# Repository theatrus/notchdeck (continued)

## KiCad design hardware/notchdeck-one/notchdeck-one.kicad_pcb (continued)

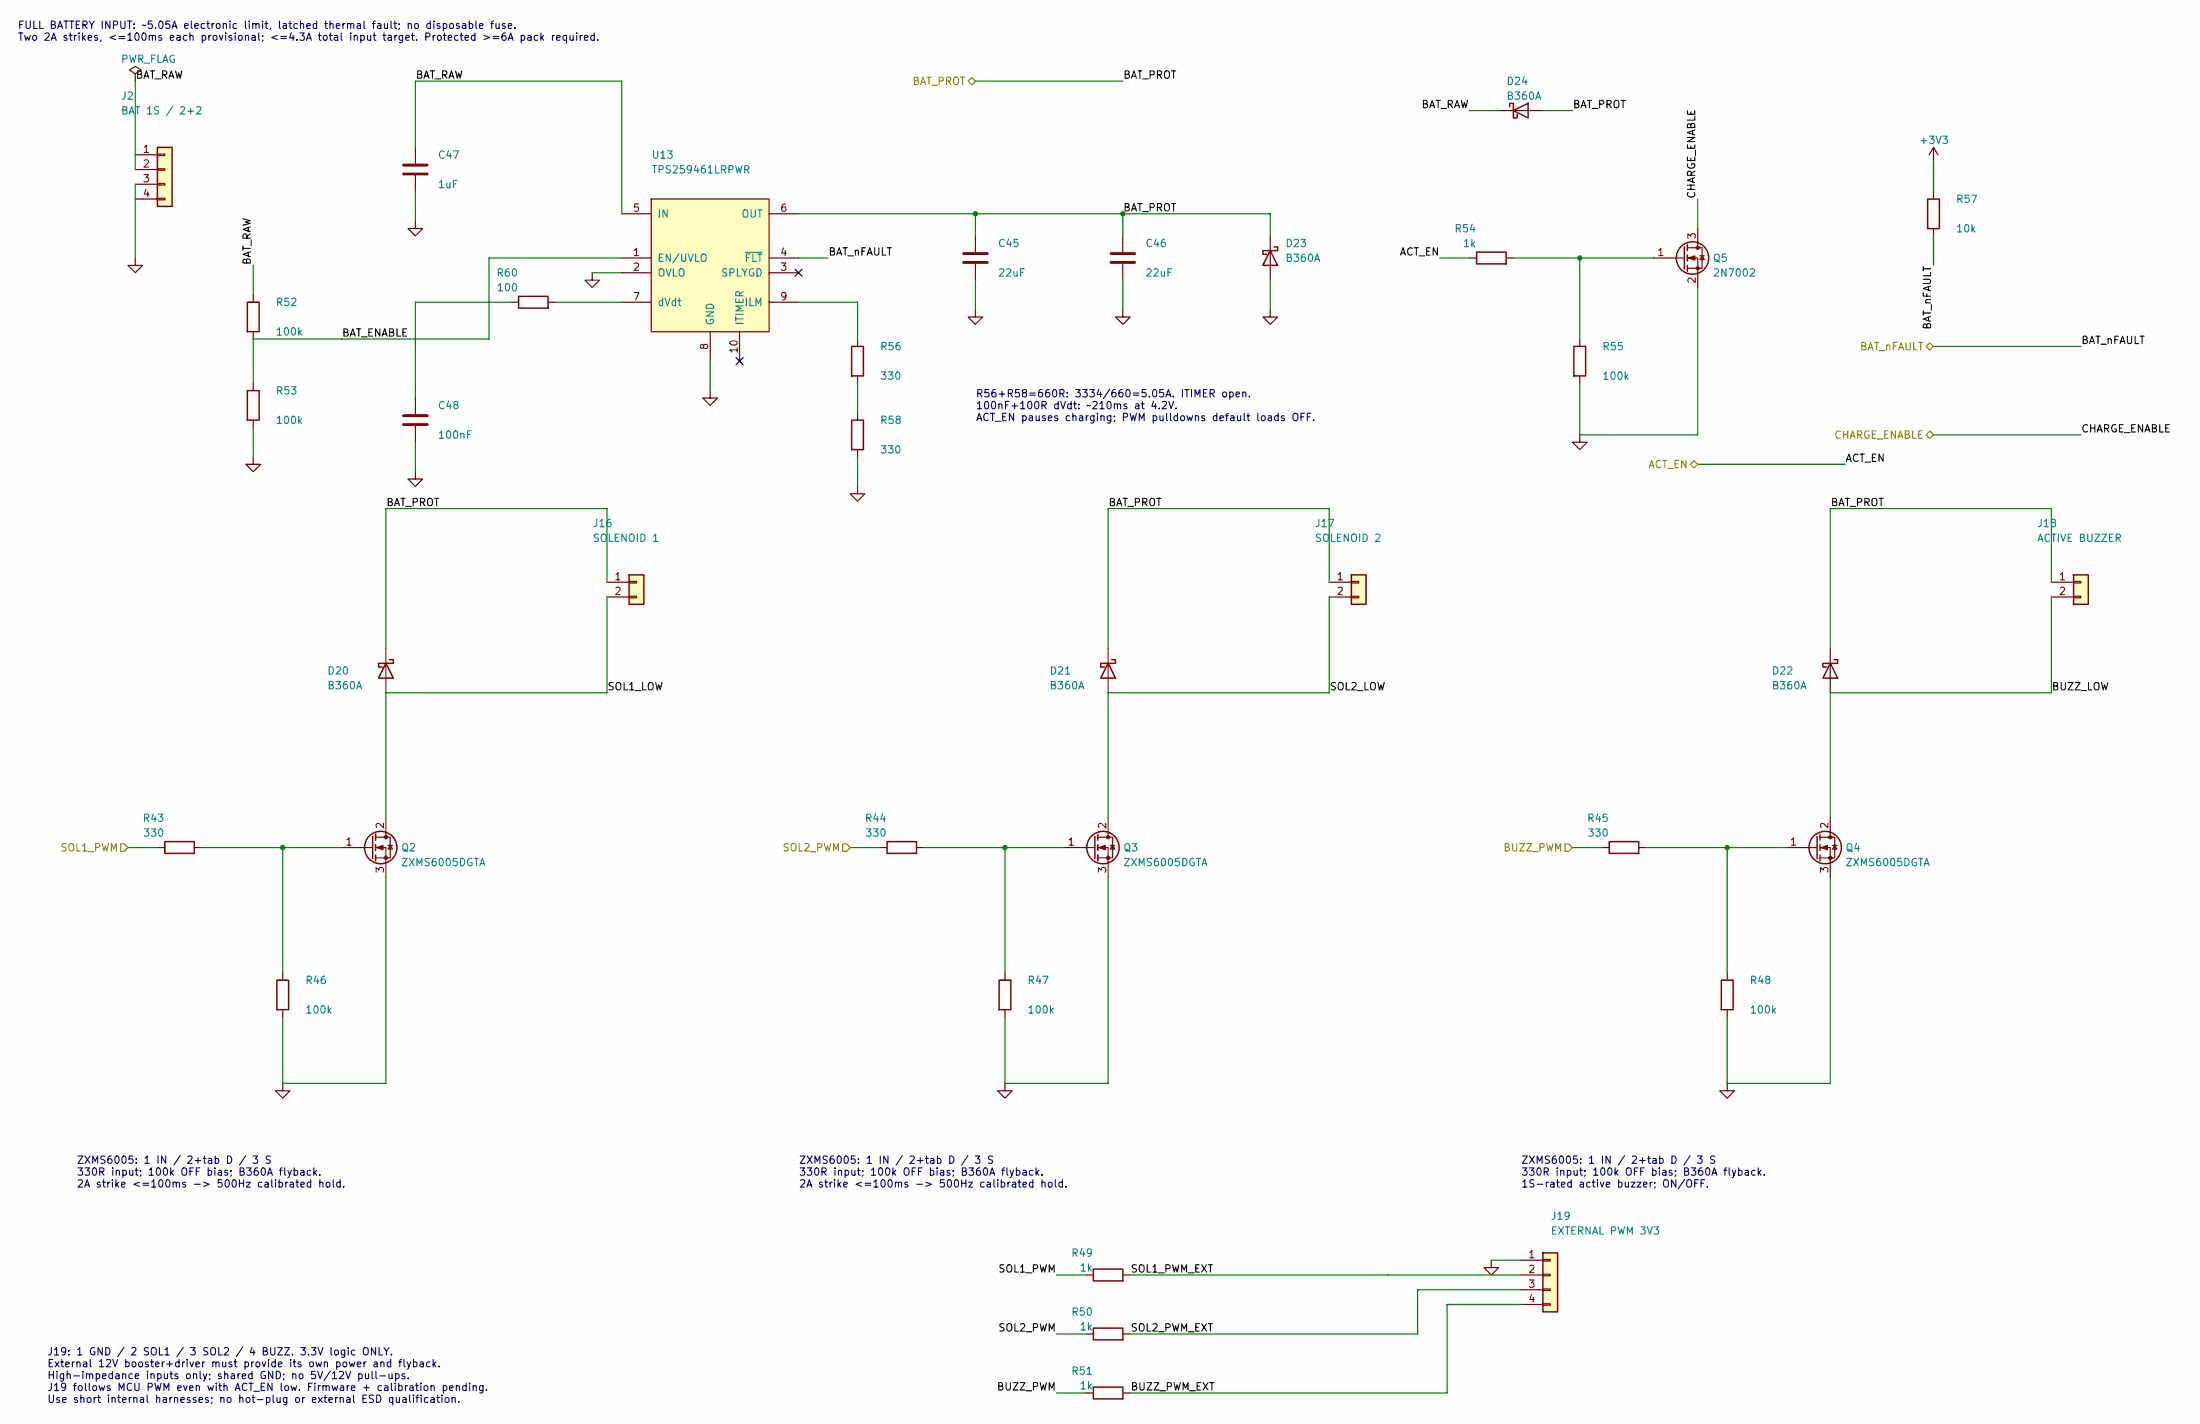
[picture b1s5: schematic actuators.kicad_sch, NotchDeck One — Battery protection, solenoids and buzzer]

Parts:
C45, C46: 22uF; C_1210_3225Metric; MPN CL32B226KAJNNNE; LCSC C309062
C47: 1uF; C_0402_1005Metric; MPN CL05A105KA5NQNC; LCSC C52923
C48: 100nF; C_0402_1005Metric; MPN CL05B104KO5NNNC; LCSC C1525
D20, D21, D22, D23, D24: B360A; D_SMA; MPN B360A; LCSC C6807778
J2: BAT 1S / 2+2; Molex_Micro-Fit_3.0_43045-0400_2x02_P3.00mm_Horizontal; MPN 430450401; LCSC C585880
J16: SOLENOID 1; JST_PH_S2B-PH-SM4-TB_1x02-1MP_P2.00mm_Horizontal; MPN S2B-PH-SM4-TB(LF)(SN); LCSC C295747
J17: SOLENOID 2; JST_PH_S2B-PH-SM4-TB_1x02-1MP_P2.00mm_Horizontal; MPN S2B-PH-SM4-TB(LF)(SN); LCSC C295747
J18: ACTIVE BUZZER; JST_PH_S2B-PH-SM4-TB_1x02-1MP_P2.00mm_Horizontal; MPN S2B-PH-SM4-TB(LF)(SN); LCSC C295747
J19: EXTERNAL PWM 3V3; JST_PH_S4B-PH-SM4-TB_1x04-1MP_P2.00mm_Horizontal; MPN S4B-PH-SM4-TB(LF)(SN); LCSC C265102
Q2, Q3, Q4: ZXMS6005DGTA; SOT-223-3_TabPin2; MPN ZXMS6005DGTA; LCSC C174045
Q5: 2N7002; SOT-23; MPN 2N7002; LCSC C8545
R43, R44, R45, R56, R58: 330; R_0402_1005Metric; MPN 0402WGF3300TCE; LCSC C25104
R46, R47, R48, R52, R53, R55: 100k; R_0402_1005Metric; MPN 0402WGF1003TCE; LCSC C25741
R49, R50, R51, R54: 1k; R_0402_1005Metric; MPN 0402WGF1001TCE; LCSC C11702
R57: 10k; R_0402_1005Metric; MPN 0402WGF1002TCE; LCSC C25744
R60: 100; R_0603_1608Metric; MPN 0603WAF1000T5E; LCSC C22775
U13: TPS259461LRPWR; TI_RPW0010A; MPN TPS259461LRPWR; LCSC C3662776

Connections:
+3V3: R57.1; also elsewhere on the board
/ACT_EN: R54.1; also elsewhere on the board
/Actuators/BAT_ENABLE: R52.2, R53.1, U13.1 (EN/UVLO)
/Actuators/BAT_RAW: C47.1, D24.1 (K), J2.1, J2.2, R52.1, U13.5 (IN)
/Actuators/BUZZ_LOW: D22.2 (A), J18.2, Q4.2 (D)
/Actuators/BUZZ_PWM_EXT: J19.4, R51.2
/Actuators/SOL1_LOW: D20.2 (A), J16.2, Q2.2 (D)
/Actuators/SOL1_PWM_EXT: J19.2, R49.2
/Actuators/SOL2_LOW: D21.2 (A), J17.2, Q3.2 (D)
/Actuators/SOL2_PWM_EXT: J19.3, R50.2
/BAT_PROT: C45.1, C46.1, D20.1 (K), D21.1 (K), D22.1 (K), D23.1 (K), D24.2 (A), J16.1, J17.1, J18.1, U13.6 (OUT); also elsewhere on the board
/BAT_nFAULT: R57.2, U13.4 (~FLT); also elsewhere on the board
/BUZZ_PWM: R45.1, R51.1; also elsewhere on the board
/CHARGE_ENABLE: Q5.3 (D); also elsewhere on the board
/SOL1_PWM: R43.1, R49.1; also elsewhere on the board
/SOL2_PWM: R44.1, R50.1; also elsewhere on the board
unnamed: C48.1, R60.1
unnamed: Q2.1 (G), R43.2, R46.1
unnamed: Q3.1 (G), R44.2, R47.1
unnamed: Q4.1 (G), R45.2, R48.1
unnamed: Q5.1 (G), R54.2, R55.1
unnamed: R56.2, R58.1
unnamed: R56.1, U13.9 (ILM)
unnamed: R60.2, U13.7 (dVdt)

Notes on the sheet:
FULL BATTERY INPUT: ~5.05A electronic limit, latched thermal fault; no disposable fuse. Two 2A strikes, <=100ms each provisional; <=4.3A total input target. Protected >=6A pack required.
R56+R58=660R: 3334/660=5.05A. ITIMER open. 100nF+100R dVdt: ~210ms at 4.2V. ACT_EN pauses charging; PWM pulldowns default loads OFF.
ZXMS6005: 1 IN / 2+tab D / 3 S 330R input; 100k OFF bias; B360A flyback. 2A strike <=100ms -> 500Hz calibrated hold.
ZXMS6005: 1 IN / 2+tab D / 3 S 330R input; 100k OFF bias; B360A flyback. 1S-rated active buzzer; ON/OFF.
J19: 1 GND / 2 SOL1 / 3 SOL2 / 4 BUZZ. 3.3V logic ONLY. External 12V booster+driver must provide its own power and flyback. High-impedance inputs only; shared GND; no 5V/12V pull-ups. J19 follows MCU PWM even with ACT_EN low. Firmware + calibration pending. Use short internal harnesses; no hot-plug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

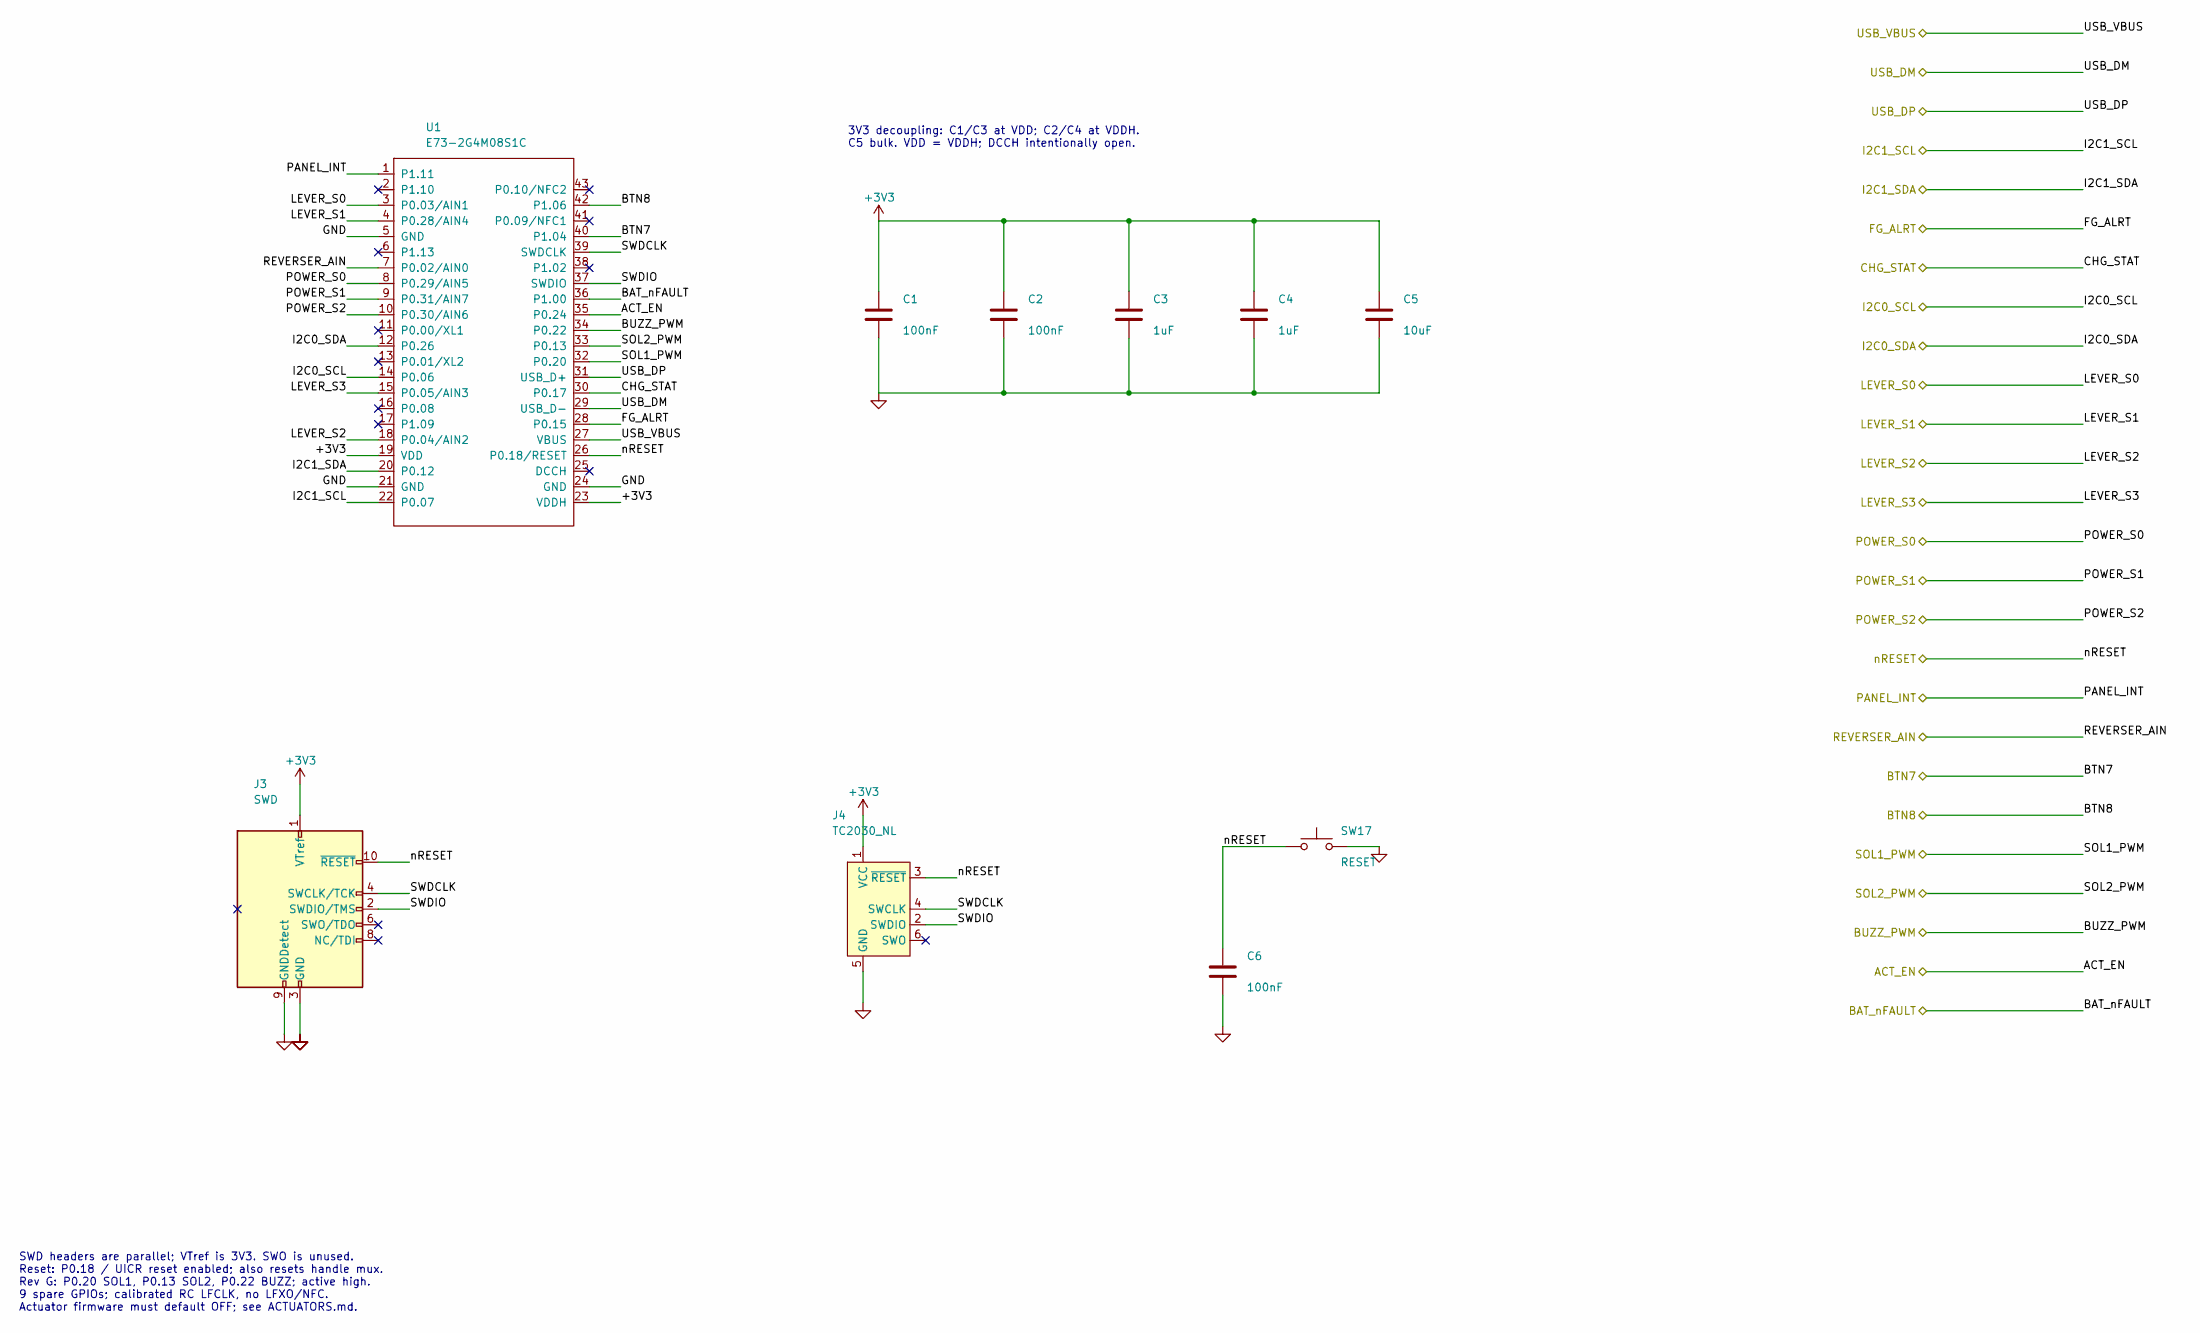
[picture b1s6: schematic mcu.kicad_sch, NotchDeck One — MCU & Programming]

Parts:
C1, C2, C6: 100nF; C_0402_1005Metric; MPN CL05B104KO5NNNC; LCSC C1525
C3, C4: 1uF; C_0402_1005Metric; MPN CL05A105KA5NQNC; LCSC C52923
C5: 10uF; C_0805_2012Metric; MPN CL21A106KAYNNNE; LCSC C15850
J3: SWD; Samtec_FTSH-105-01-L-DV-K; MPN FTSH-105-01-L-DV-K-TR; LCSC C448647
J4: TC2030_NL; Tag-Connect_TC2030-IDC-NL_2x03_P1.27mm_Vertical
SW17: RESET; SW_Push_1P1T_XKB_TS-1187A; MPN TS-1187A-B-A-B; LCSC C318884
U1: E73-2G4M08S1C; EBYTE_E73-2G4M08S1C; MPN E73-2G4M08S1C; LCSC C356849

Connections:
+3V3: C1.1, C2.1, C3.1, C4.1, C5.1, J3.1 (VTref), J4.1 (VCC), U1.19 (VDD), U1.23 (VDDH); also elsewhere on the board
/ACT_EN: U1.35 (P0.24); also elsewhere on the board
/BAT_nFAULT: U1.36 (P1.00); also elsewhere on the board
/BTN7: U1.40 (P1.04); also elsewhere on the board
/BTN8: U1.42 (P1.06); also elsewhere on the board
/BUZZ_PWM: U1.34 (P0.22); also elsewhere on the board
/CHG_STAT: U1.30 (P0.17); also elsewhere on the board
/FG_ALRT: U1.28 (P0.15); also elsewhere on the board
/I2C0_SCL: U1.14 (P0.06); also elsewhere on the board
/I2C0_SDA: U1.12 (P0.26); also elsewhere on the board
/I2C1_SCL: U1.22 (P0.07); also elsewhere on the board
/I2C1_SDA: U1.20 (P0.12); also elsewhere on the board
/LEVER_S0: U1.3 (P0.03/AIN1); also elsewhere on the board
/LEVER_S1: U1.4 (P0.28/AIN4); also elsewhere on the board
/LEVER_S2: U1.18 (P0.04/AIN2); also elsewhere on the board
/LEVER_S3: U1.15 (P0.05/AIN3); also elsewhere on the board
/MCU/SWDCLK: J3.4 (SWCLK/TCK), J4.4 (SWCLK), U1.39 (SWDCLK)
/MCU/SWDIO: J3.2 (SWDIO/TMS), J4.2 (SWDIO), U1.37 (SWDIO)
/PANEL_INT: U1.1 (P1.11); also elsewhere on the board
/POWER_S0: U1.8 (P0.29/AIN5); also elsewhere on the board
/POWER_S1: U1.9 (P0.31/AIN7); also elsewhere on the board
/POWER_S2: U1.10 (P0.30/AIN6); also elsewhere on the board
/REVERSER_AIN: U1.7 (P0.02/AIN0); also elsewhere on the board
/SOL1_PWM: U1.32 (P0.20); also elsewhere on the board
/SOL2_PWM: U1.33 (P0.13); also elsewhere on the board
/USB_DM: U1.29 (USB_D-); also elsewhere on the board
/USB_DP: U1.31 (USB_D+); also elsewhere on the board
/nRESET: C6.1, J3.10 (~RESET), J4.3 (~RESET), SW17.1, U1.26 (P0.18/RESET); also elsewhere on the board

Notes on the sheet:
3V3 decoupling: C1/C3 at VDD; C2/C4 at VDDH. C5 bulk. VDD = VDDH; DCCH intentionally open.
SWD headers are parallel; VTref is 3V3. SWO is unused. Reset: P0.18 / UICR reset enabled; also resets handle mux. Rev G: P0.20 SOL1, P0.13 SOL2, P0.22 BUZZ; active high. 9 spare GPIOs; calibrated RC LFCLK, no LFXO/NFC. Actuator firmware must default OFF; see ACTUATORS.md.

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
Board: 4 copper layers, 134 parts (0 on the bottom side), 72 nets, no tracks yet.

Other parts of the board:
H1, H2, H3, H4: M3 provisional; MountingHole_3.2mm_M3

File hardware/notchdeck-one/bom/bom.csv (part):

Reference,Qty,Value,Footprint,MPN,Manufacturer,LCSC,LC_Stock,Chosen_Distributor,Datasheet,Validated,DNP,Notes
"C1,C2,C6,C10,C11,C14,C15,C16,C17,C37,C38,C39,C40,C41,C42,C43,C44,C48",18,100nF,0402,CL05B104KO5NNNC,Samsung Electro-Mechanics,C1525,,JLCPCB,https://datasheet.lcsc.com/datasheet/pdf/02336ea48ea44ca18c7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,Yes,,100nF 16V X7R ±10% 0402 Multilayer Ceramic Capacitors MLCC - SMD/SMT ROHS
"C3,C4,C7,C8,C12,C47",6,1uF,0402,CL05A105KA5NQNC,Samsung Electro-Mechanics,C52923,,JLCPCB,https://datasheet.lcsc.com/datasheet/pdf/02336ea48ea44ca18c7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,Yes,,1uF 25V X5R ±10% 0402 Multilayer Ceramic Capacitors MLCC - SMD/SMT ROHS
"C5,C9",2,10uF,0805,CL21A106KAYNNNE,Samsung Electro-Mechanics,C15850,,JLCPCB,https://datasheet.lcsc.com/datasheet/pdf/02336ea48ea44ca18c7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,Yes,,10uF 25V X5R ±10% 0805 Multilayer Ceramic Capacitors MLCC - SMD/SMT ROHS
"C18,C19",2,4.7uF,0805,CL21A475KAQNNNE,Samsung Electro-Mechanics,C1779,,JLCPCB,https://datasheet.lcsc.com/datasheet/pdf/02336ea48ea44ca18c7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,Yes,,25V 4.7uF X5R ±10% 0805 Multilayer Ceramic Capacitors MLCC - SMD/SMT ROHS
"C45,C46",2,22uF,1210,CL32B226KAJNNNE,Samsung Electro-Mechanics,C309062,,JLCPCB,https://datasheet.lcsc.com/datasheet/pdf/02336ea48ea44ca18c7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,Yes,,22uF/25V X7R bulk; allow DC-bias derating; near actuator connectors.
D17,1,LED,0603,XL-1608SYGC-06,XINGLIGHT,C965805,,JLCPCB,https://datasheet.lcsc.com/datasheet/pdf/db39074692074ba57d4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,Yes,,
D18,1,LED,0603,KT-0603R,Hubei KENTO Elec,C2286,,JLCPCB,https://datasheet.lcsc.com/datasheet/pdf/011ec3e8cb1e825f696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,Yes,,
D19,1,B5819W,SOD-123,B5819W SL,JSCJ,C8598,,JLCPCB,https://datasheet.lcsc.com/datasheet/pdf/4ac2c059be7c462694a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,Yes,,
"D20,D21,D22,D23,D24",5,B360A,SMA(DO-214AC),B360A,FUXINSEMI,C6807778,,JLCPCB,https://datasheet.lcsc.com/datasheet/pdf/4341698a2794575dc7c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,Yes,,D20-D22 flyback K=BAT_PROT/A=load return; D23 clamp K=BAT_PROT/A=GND; D24 charging recovery K=BAT_RAW/A=BAT_PROT.
J1,1,USB-C,SMD,TYPE-C-31-M-12,Korean Hroparts Elec,C165948,,JLCPCB,https://datasheet.lcsc.com/datasheet/pdf/9e56b777c022540fcce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,Yes,,
J2,1,BAT 1S / 2+2,THT right-angle 2x2 3mm,430450401,Molex,C585880,,JLCPCB,https://datasheet.lcsc.com/datasheet/pdf/b6e3df063c26f8567b2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,Yes,,"Owned Micro-Fit battery inlet: 1+2 positive, 3+4 GND. Populate both contacts per polarity with 20AWG leads. THT assembly."
J3,1,SWD,"SMD,P=1.27mm",FTSH-105-01-L-DV-K-TR,Samtec,C448647,,JLCPCB,https://datasheet.lcsc.com/datasheet/pdf/75565f450863f224a13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,Yes,,Samtec keyed shroud; manufacturer land pattern. Check JLCPCB fixture requirement and CPL rotation.
J5,1,BRAKE / MASCON GRAY,"SMD,P=2mm,Right Angle",S6B-PH-SM4-TB(LF)(SN),JST,C265405,,JLCPCB,https://datasheet.lcsc.com/datasheet/pdf/fd6b0599884a99953f0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,Yes,,"Rev D brake/mascon Gray harness: pin1=GND, pins2..5=S0..S3, pin6=3V3. Passive cams leave supply cavity empty. Mating PHR-6 housing/crimps separate."
J9,1,REV F-N-R,"SMD,P=2mm,卧贴",S3B-PH-SM4-TB(LF)(SN),JST,C265101,,JLCPCB,https://datasheet.lcsc.com/datasheet/pdf/6c6fce4367275d84ec6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,Yes,,External center-off reverser and mating harness not included.
J10,1,POWER MAG,"SMD,P=2mm,卧贴",S4B-PH-SM4-TB(LF)(SN),JST,C265102,,JLCPCB,https://datasheet.lcsc.com/datasheet/pdf/6c6fce4367275d84ec6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,Yes,,"3.3V magnetic handle: pin 1=3V3, 2=GND, 3=SDA, 4=SCL. Mating harness/sensor separate."
J11,1,BRAKE MAG,"SMD,P=2mm,卧贴",S4B-PH-SM4-TB(LF)(SN),JST,C265102,,JLCPCB,https://datasheet.lcsc.com/datasheet/pdf/6c6fce4367275d84ec6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,Yes,,"3.3V magnetic handle: pin 1=3V3, 2=GND, 3=SDA, 4=SCL. Mating harness/sensor separate."
J12,1,POWER GRAY,"SMD,P=2mm,Right Angle",S5B-PH-SM4-TB(LF)(SN),JST,C265104,,JLCPCB,https://datasheet.lcsc.com/datasheet/pdf/d87682fbfaf1a1bc6a2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,Yes,,"Rev D power Gray harness: pin1=GND, pins2..4=S0..S2, pin5=3V3. Passive cams leave supply cavity empty. Mating PHR-5 housing/crimps separate."
J15,1,BUTTON MCU FFC,"SMD,P=1mm,卧贴",AFA07-S06FCA-00,JUSHUO,C262712,,JLCPCB,https://datasheet.lcsc.com/datasheet/pdf/b01391708457137d9b8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,Yes,,6-way 1mm bottom-contact FFC. Molex 0151670213 Type A cable: main J15 pin n -> button J1 pin 7-n. Cable bought once per set from DigiKey; power off to insert.
J16,1,SOLENOID 1,"SMD,P=2mm,卧贴",S2B-PH-SM4-TB(LF)(SN),JST,C295747,,JLCPCB,https://datasheet.lcsc.com/datasheet/pdf/2474e9261ed7c5f86b5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,Yes,,"Two-pin JST PH battery connector. Pin1=BAT+, pin2=GND. Mating harness separate."
J17,1,SOLENOID 2,"SMD,P=2mm,卧贴",S2B-PH-SM4-TB(LF)(SN),JST,C295747,,JLCPCB,https://datasheet.lcsc.com/datasheet/pdf/2474e9261ed7c5f86b5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,Yes,,"Two-pin JST PH battery connector. Pin1=BAT+, pin2=GND. Mating harness separate."
J18,1,ACTIVE BUZZER,"SMD,P=2mm,卧贴",S2B-PH-SM4-TB(LF)(SN),JST,C295747,,JLCPCB,https://datasheet.lcsc.com/datasheet/pdf/2474e9261ed7c5f86b5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,Yes,,"Two-pin JST PH battery connector. Pin1=BAT+, pin2=GND. Mating harness separate."
J19,1,EXTERNAL PWM 3V3,"SMD,P=2mm,卧贴",S4B-PH-SM4-TB(LF)(SN),JST,C265102,,JLCPCB,https://datasheet.lcsc.com/datasheet/pdf/6c6fce4367275d84ec6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,Yes,,"3.3V magnetic handle: pin 1=3V3, 2=GND, 3=SDA, 4=SCL. Mating harness/sensor separate."
Q1,1,AO3401A,SOT-23,AO3401A,AOS,C15127,,JLCPCB,https://datasheet.lcsc.com/datasheet/pdf/fee353dd1e9e0bc90b2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,Yes,,
"Q2,Q3,Q4",3,ZXMS6005DGTA,SOT-223-3,ZXMS6005DGTA,DIODES,C174045,,JLCPCB,https://datasheet.lcsc.com/datasheet/pdf/f028d27543061fafe3e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,Yes,,"Protected low-side FET; pin 1 IN, pin 2/tab D, pin 3 S. 3V minimum input; 500Hz solenoid PWM target; qualify low-battery drive and thermal margins."
"Q5,Q6",2,2N7002,SOT-23,2N7002,JSCJ,C8545,,JLCPCB,https://datasheet.lcsc.com/datasheet/pdf/a141b8bd86b14475955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,Yes,,Charger PROG interlock: suspend charging while actuator bank is enabled
"R1,R2",2,5.1k,0402,0402WGF5101TCE,UNI-ROYAL,C25905,,JLCPCB,https://datasheet.lcsc.com/datasheet/pdf/0a975aaa49b7c97f38a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,Yes,,-55℃~+155℃ 5.1kΩ 50V 62.5mW Thick Film Resistor ±1% ±100ppm/℃ 0402 Chip Resistor - Surface Mount ROHS
R3,1,2k,0402,0402WGF2001TCE,UNI-ROYAL,C4109,,JLCPCB,https://datasheet.lcsc.com/datasheet/pdf/0a975aaa49b7c97f38a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,Yes,,-55℃~+155℃ 2kΩ 50V 62.5mW Thick Film Resistor ±1% ±100ppm/℃ 0402 Chip Resistor - Surface Mount ROHS
"R4,R8,R22,R23,R24,R46,R47,R48,R52,R53,R55,R59",12,100k,0402,0402WGF1003TCE,UNI-ROYAL,C25741,,JLCPCB,https://datasheet.lcsc.com/datasheet/pdf/0a975aaa49b7c97f38a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,Yes,,-55℃~+155℃ 100kΩ 50V 62.5mW Thick Film Resistor ±1% ±100ppm/℃ 0402 Chip Resistor - Surface Mount ROHS
"R5,R12,R13,R18,R19,R20,R21,R25,R34,R35,R36,R49,R50,R51,R54",15,1k,0402,0402WGF1001TCE,UNI-ROYAL,C11702,,JLCPCB,https://datasheet.lcsc.com/datasheet/pdf/0a975aaa49b7c97f38a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,Yes,,-55℃~+155℃ 1kΩ 50V 62.5mW Thick Film Resistor ±1% ±100ppm/℃ 0402 Chip Resistor - Surface Mount ROHS
"R6,R7,R9,R10,R27,R28,R29,R30",8,4.7k,0402,0402WGF4701TCE,UNI-ROYAL,C25900,,JLCPCB,https://datasheet.lcsc.com/datasheet/pdf/0a975aaa49b7c97f38a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,Yes,,-55℃~+155℃ 4.7kΩ 50V 62.5mW Thick Film Resistor ±1% ±100ppm/℃ 0402 Chip Resistor - Surface Mount ROHS
"R14,R15,R16,R17,R31,R32,R33,R39,R40,R41,R42,R57",12,10k,0402,0402WGF1002TCE,UNI-ROYAL,C25744,,JLCPCB,https://datasheet.lcsc.com/datasheet/pdf/0a975aaa49b7c97f38a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,Yes,,-55℃~+155℃ 10kΩ 50V 62.5mW Thick Film Resistor ±1% ±100ppm/℃ 0402 Chip Resistor - Surface Mount ROHS
"R37,R38",2,0,0603,0603WAF0000T5E,UNI-ROYAL,C21189,,JLCPCB,https://datasheet.lcsc.com/datasheet/pdf/f42da6c80a0747bae77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,Yes,,Remove BOTH R37/R38 before connecting an external power AS5600 to J10; isolates onboard U5.
"R43,R44,R45,R56,R58",5,330,0402,0402WGF3300TCE,UNI-ROYAL,C25104,,JLCPCB,https://datasheet.lcsc.com/datasheet/pdf/0a975aaa49b7c97f38a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,Yes,,-55℃~+155℃ 330Ω 50V 62.5mW Thick Film Resistor ±1% ±100ppm/℃ 0402 Chip Resistor - Surface Mount ROHS
R60,1,100,0603,0603WAF1000T5E,UNI-ROYAL,C22775,,JLCPCB,https://datasheet.lcsc.com/datasheet/pdf/0a975aaa49b7c97f38a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,Yes,,100 ohm resistor in series with 100nF DVDT capacitor as TI recommends for >10nF. Existing private stock is reserved; top-up required.
SW17,1,RESET,"SMD-4P,5.1x5.1mm",TS-1187A-B-A-B,XKB Connection,C318884,,JLCPCB,https://datasheet.lcsc.com/datasheet/pdf/56c8799ae5193945a16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,Yes,,
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
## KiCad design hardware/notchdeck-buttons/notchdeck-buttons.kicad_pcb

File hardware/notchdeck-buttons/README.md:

# NotchDeck Buttons — Rev E

An independent 4×4 key/RGB assembly driven by **STM32G030F6P6TR (C529330)** from owned JLCPCB stock. It connects to the logic board through a six-conductor FFC. The schematic is wired and checked; the 86×120mm two-layer PCB is an **unrouted floorplan**. Panel firmware and main-controller integration are not implemented yet.

## Connector and cable

Both connectors are **JUSHUO AFA07-S06FCA-00 / C262712**, 6 contacts, 1mm pitch, bottom contact, nominal 0.30mm FFC ends. Use **Molex 0151670213**, DigiKey **WM13121-ND**, Type A same-side exposed contacts, 177.8mm long. Five cables are listed in the [system BOM](../system-bom.csv); the assembly BOMs contain only the PCB connectors.

Identical bottom-contact connectors at opposite ends of a Type A cable reverse connector numbering. The schematic compensates deliberately: **main pin n connects to button pin 7−n**. Insert exposed contacts toward each PCB; power off for insertion/removal. This is an internal enclosure interconnect.

| Main J15 | Signal | Button J1 |
|---:|---|---:|
| 1 | GND | 6 |
| 2 | 3V3 — MCU and keys, including battery operation | 5 |
| 3 | SDA — I2C0 on main, I2C1 PB7 AF6 on panel | 4 |
| 4 | SCL — I2C0 on main, I2C1 PB6 AF6 on panel | 3 |
| 5 | IRQ_N — PC15 open drain to E73 P1.11 | 2 |
| 6 | USB_VBUS — RGB only | 1 |

The [JUSHUO family specification](https://datasheet.lcsc.com/datasheet/pdf/8c3225c8bd3c5aba9addae56ddc79a88.pdf?productCode=C262714) explicitly covers AFA07-S**FCA-00 and rates contacts at 0.5A. The [Molex family specification](https://www.molex.com/content/dam/molex/molex-dot-com/products/automated/en-us/productspecificationpdf/151/15167/PS-15167-001-001.pdf) rates the cable at 0.8A per conductor at 23°C; the connector limits this link. Target **≤250mA total panel return current**, including 3V3 and LED loads, subject to the main USB/charger budget. This is a firmware/current-budget requirement, not an implemented hardware limit. Full-white unrestricted LEDs are not supported by this budget.

Pitch, contact side and nominal end thickness agree with the drawings. JUSHUO specifies 0.30±0.03mm cable thickness; Molex guarantees 0.30±0.05mm ends, so worst-case tolerance compatibility is **not established**. Validate insertion, retention and contact resistance on samples, or obtain supplier approval before production. Confirm end-to-end pin numbering with a continuity check before first power. Stock: JLCPCB 31,746 available connectors; DigiKey 139 cables on 2026-10-03, before reservations/attrition.

## MCU pin plan

| U1 pad | Selected GPIO/function | Net |
|---:|---|---|
| 1 | PB7 / I2C1_SDA AF6 | SDA |
| 3 | PC15 open drain | IRQ_N |
| 4 / 5 | VDD / VSS | 3V3 / GND |
| 6 | NRST | 10k pull-up, 100nF, J2 reset |
| 7–10 | PA0–PA3 | ROW0–ROW3 |
| 11–14 | PA4–PA7 | COL0–COL3, external 10k pull-ups |
| 15 | PA8 / TIM1_CH1 AF2 | RGB_PWM → AHCT U8 |
| 17 | PA12 / ADC_IN16 | VBUS_SENSE, 100k/100k divider and 100nF |
| 18 / 19 | PA13 / PA14 | SWDIO / SWCLK |
| 20 | PB6 / I2C1_SCL AF6 | SCL |

Pads 2 and 16 are intentionally unused. On internally bonded pads, leave the unused PB8, PB3/PB4/PB5, PB0/PB1/PB2, PA10 and PA15 aliases analog/high impedance. SWD must remain enabled, and boot option bytes must select user flash without sacrificing PA14 SWCLK. Use HSI/PLL; no crystal or external flash is required. Evidence: [ST DS12991](https://www.st.com/resource/en/datasheet/stm32g030f6.pdf), pin/alternate-function and package tables. Stock identity/footprint checked against the selected TSSOP-20 ordering code.

Each key has a 1N4148W: column → switch → diode anode → cathode → row. Pull one row low, leave the other rows high impedance, wait for settling, then read four active-low columns. This orientation supports simultaneous keys without ghost paths. SW1–SW12 retain BTN1–BTN12; SW13–SW16 are Up, Down, Left, Right. Physical button pitch is 19mm.

The local AHCT buffer and RGB chain use USB_VBUS. The MCU uses 3V3, so key input works on battery. Use the VBUS divider as an ADC input, not a digital threshold. Hold RGB_PWM low whenever USB is absent and at reset; R26 provides the default pull-down. J2 is bare TC2030-NL SWD access, excluded from assembly: 1=3V3, 2=SWDIO, 3=NRST, 4=SWCLK, 5=GND, 6=NC. Program the MCU via SWD; there is no panel USB connector or implemented I²C bootloader.

## Firmware interface to implement

Use I²C target address **0x20** on the upstream main I2C0 bus at 100kHz. Main R9/R10 provide its only pull-ups. The handle mux remains 0x70 and selected magnetic sensor 0x36; the fuel gauge remains on separate I2C1. Start with a 1kHz complete matrix scan, roughly 10ms stable-state debounce, and an atomic 16-bit pressed-key bitmap with a sequence counter. Assert IRQ until the latest stable state is acknowledged, avoiding a lost update when a key changes during a read. Retain a periodic poll as a fallback.

Define a versioned register/packet contract before implementing either side. Include LED frame/brightness commands and status (VBUS, firmware version, faults); use timer/DMA so RGB generation does not block I²C service. On communications loss, main releases panel keys and panel turns LEDs off. OR main SW18/SW19 into Select/Start so either physical location works. Define low-power scanning/wake behavior for BLE use and test rollover, debounce, reset during transfer, cable disconnect, brownout and USB removal. No wire protocol or executable panel firmware is claimed by this hardware revision.

## Checks

`make -C hardware verify` verifies both assemblies. Panel audit covers 85 components, 56 nets, 235 endpoints, four intentional NCs and every FFC conductor; native ERC has zero errors/warnings. BOM/CPL contains 84 parts (13 catalog codes). See [floorplan](FLOORPLAN.md) for placement/routing status.

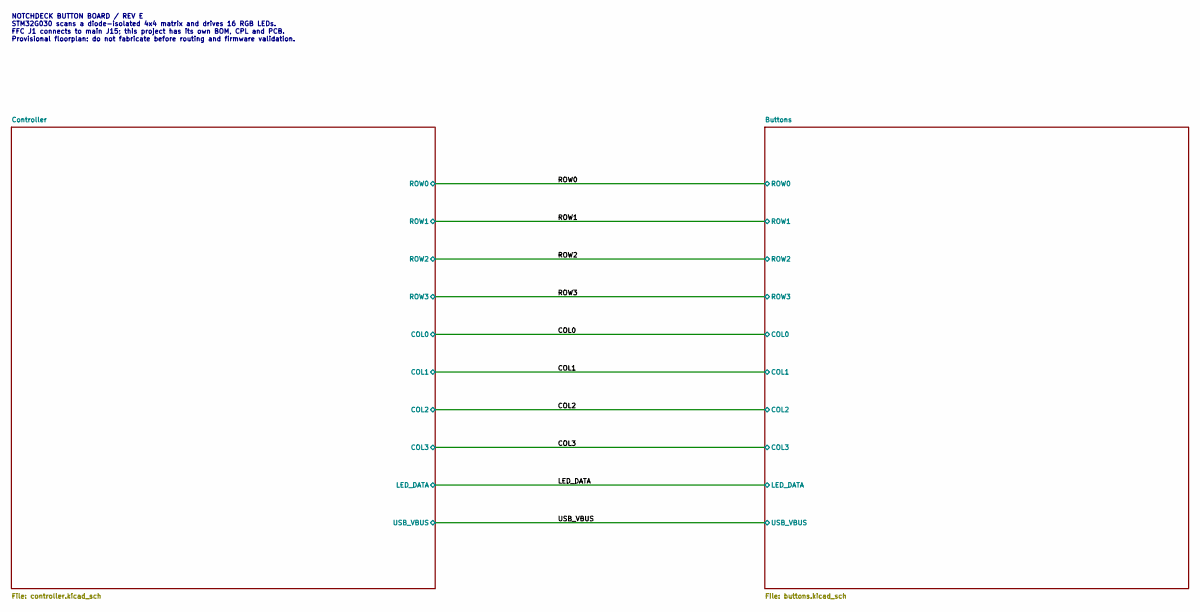
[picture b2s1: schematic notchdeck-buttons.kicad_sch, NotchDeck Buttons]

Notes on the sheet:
NOTCHDECK BUTTON BOARD / REV E STM32G030 scans a diode-isolated 4x4 matrix and drives 16 RGB LEDs. FFC J1 connects to main J15; this project has its own BOM, CPL and PCB. Provisional floorplan: do not fabricate before routing and firmware validation.

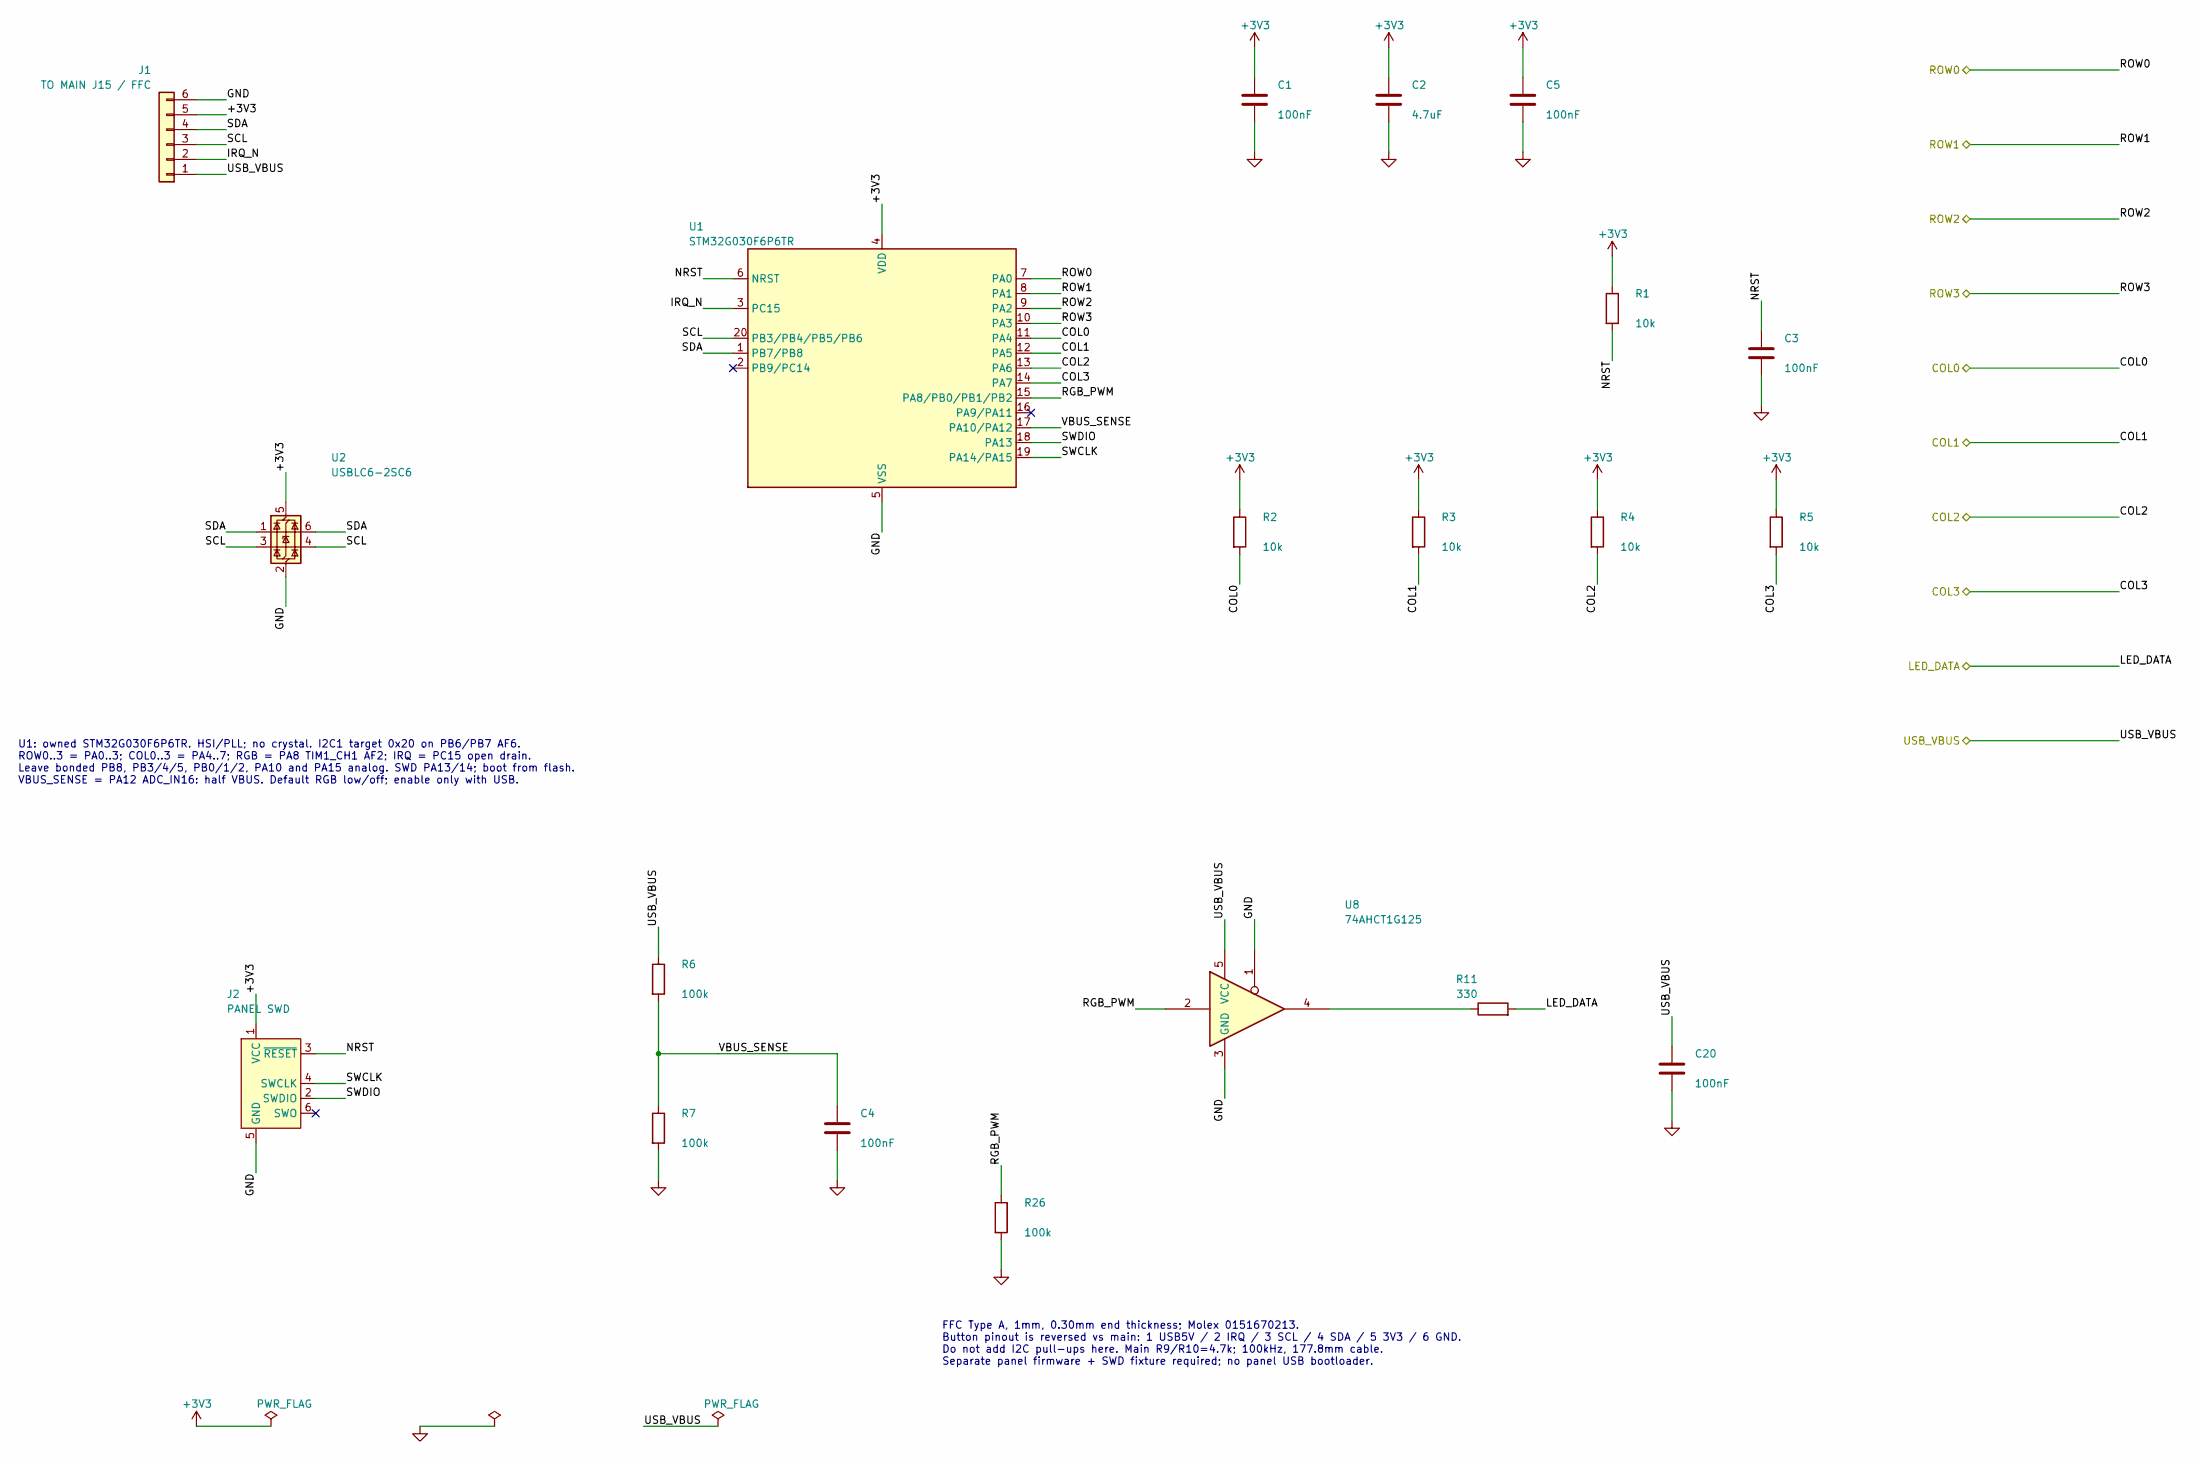
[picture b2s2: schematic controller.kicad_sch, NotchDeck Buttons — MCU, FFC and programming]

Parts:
C1, C3, C4, C5, C20: 100nF; C_0402_1005Metric; MPN CL05B104KO5NNNC; LCSC C1525
C2: 4.7uF; C_0805_2012Metric; MPN CL21A475KAQNNNE; LCSC C1779
J1: TO MAIN J15 / FFC; JUSHUO_AFA07-S06FCA-00_1x6-1MP_P1.0mm_Horizontal; MPN AFA07-S06FCA-00; LCSC C262712
J2: PANEL SWD; Tag-Connect_TC2030-IDC-NL_2x03_P1.27mm_Vertical
R1, R2, R3, R4, R5: 10k; R_0402_1005Metric; MPN 0402WGF1002TCE; LCSC C25744
R6, R7, R26: 100k; R_0402_1005Metric; MPN 0402WGF1003TCE; LCSC C25741
R11: 330; R_0402_1005Metric; MPN 0402WGF3300TCE; LCSC C25104
U1: STM32G030F6P6TR; TSSOP-20_4.4x6.5mm_P0.65mm; MPN STM32G030F6P6TR; LCSC C529330
U2: USBLC6-2SC6; SOT-23-6; MPN USBLC6-2SC6; LCSC C7519
U8: 74AHCT1G125; SOT-23-5; MPN SN74AHCT1G125DBVR; LCSC C7484

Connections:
/COL0: R2.2, U1.11 (PA4); also elsewhere on the board
/COL1: R3.2, U1.12 (PA5); also elsewhere on the board
/COL2: R4.2, U1.13 (PA6); also elsewhere on the board
/COL3: R5.2, U1.14 (PA7); also elsewhere on the board
/Controller/IRQ_N: J1.2, U1.3 (PC15)
/Controller/NRST: C3.1, J2.3 (~RESET), R1.2, U1.6 (NRST)
/Controller/RGB_PWM: R26.1, U1.15 (PA8/PB0/PB1/PB2), U8.2
/Controller/SCL: J1.3, U1.20 (PB3/PB4/PB5/PB6), U2.3 (I/O2), U2.4 (I/O2)
/Controller/SDA: J1.4, U1.1 (PB7/PB8), U2.1 (I/O1), U2.6 (I/O1)
/Controller/SWCLK: J2.4 (SWCLK), U1.19 (PA14/PA15)
/Controller/SWDIO: J2.2 (SWDIO), U1.18 (PA13)
/Controller/VBUS_SENSE: C4.1, R6.2, R7.1, U1.17 (PA10/PA12)
/LED_DATA: R11.2; also elsewhere on the board
/ROW0: U1.7 (PA0); also elsewhere on the board
/ROW1: U1.8 (PA1); also elsewhere on the board
/ROW2: U1.9 (PA2); also elsewhere on the board
/ROW3: U1.10 (PA3); also elsewhere on the board
unnamed: R11.1, U8.4

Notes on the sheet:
U1: owned STM32G030F6P6TR. HSI/PLL; no crystal. I2C1 target 0x20 on PB6/PB7 AF6. ROW0..3 = PA0..3; COL0..3 = PA4..7; RGB = PA8 TIM1_CH1 AF2; IRQ = PC15 open drain. Leave bonded PB8, PB3/4/5, PB0/1/2, PA10 and PA15 analog. SWD PA13/14; boot from flash. VBUS_SENSE = PA12 ADC_IN16: half VBUS. Default 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
FFC Type A, 1mm, 0.30mm end thickness; Molex 0151670213. Button pinout is reversed vs main: 1 USB5V / 2 IRQ / 3 SCL / 4 SDA / 5 3V3 / 6 GND. Do not add I2C pull-ups here. Main R9/R10=4.7k; 100kHz, 177.8mm cable. Separate panel firmware + SWD fixture required; no panel USB bootloader.
